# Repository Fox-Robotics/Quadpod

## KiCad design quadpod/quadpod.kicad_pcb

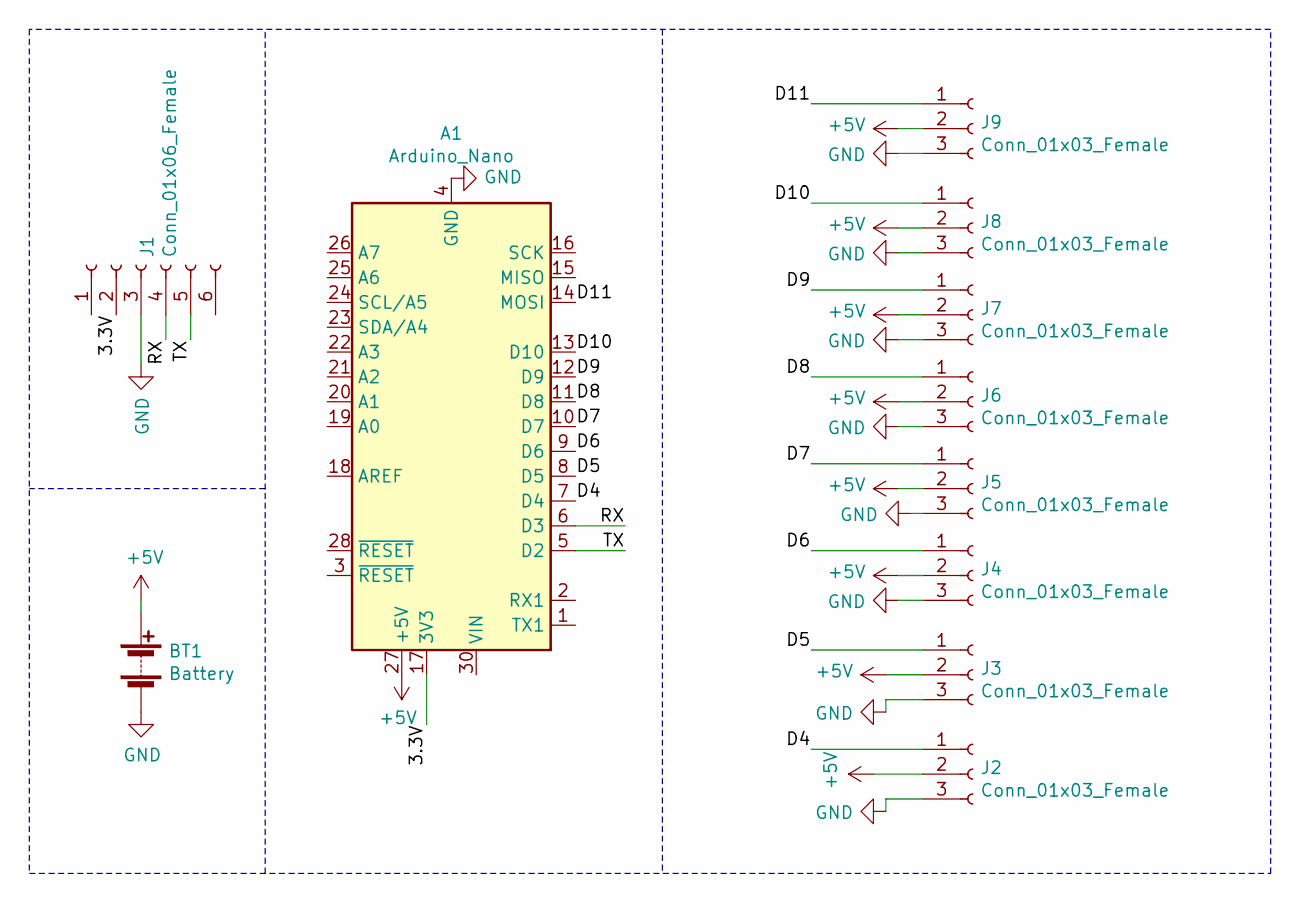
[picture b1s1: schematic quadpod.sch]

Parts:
A1: Arduino_Nano
BT1: Battery; Arduino_Nano
J1: Conn_01x06_Female; Pin_Header_Straight_1x06_Pitch1.27mm
J2, J3, J4, J5, J6, J7, J8, J9: Conn_01x03_Female; Pin_Header_Straight_1x03_Pitch1.27mm

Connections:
+5V: A1.27 (+5V), BT1.1 (+), J2.2, J3.2, J4.2, J5.2, J6.2, J7.2, J8.2, J9.2
/3.3V: A1.17 (3V3), J1.2
/D4: A1.7 (D4), J2.1
/D5: A1.8 (D5), J3.1
/D6: A1.9 (D6), J4.1
/D7: A1.10 (D7), J5.1
/D8: A1.11 (D8), J6.1
/D9: A1.12 (D9), J7.1
/D10: A1.13 (D10), J8.1
/D11: A1.14 (MOSI), J9.1
/RX: A1.6 (D3), J1.4
/TX: A1.5 (D2), J1.5
GND: A1.4 (GND), A1.29 (GND), BT1.2 (-), J1.3, J2.3, J3.3, J4.3, J5.3, J6.3, J7.3, J8.3, J9.3

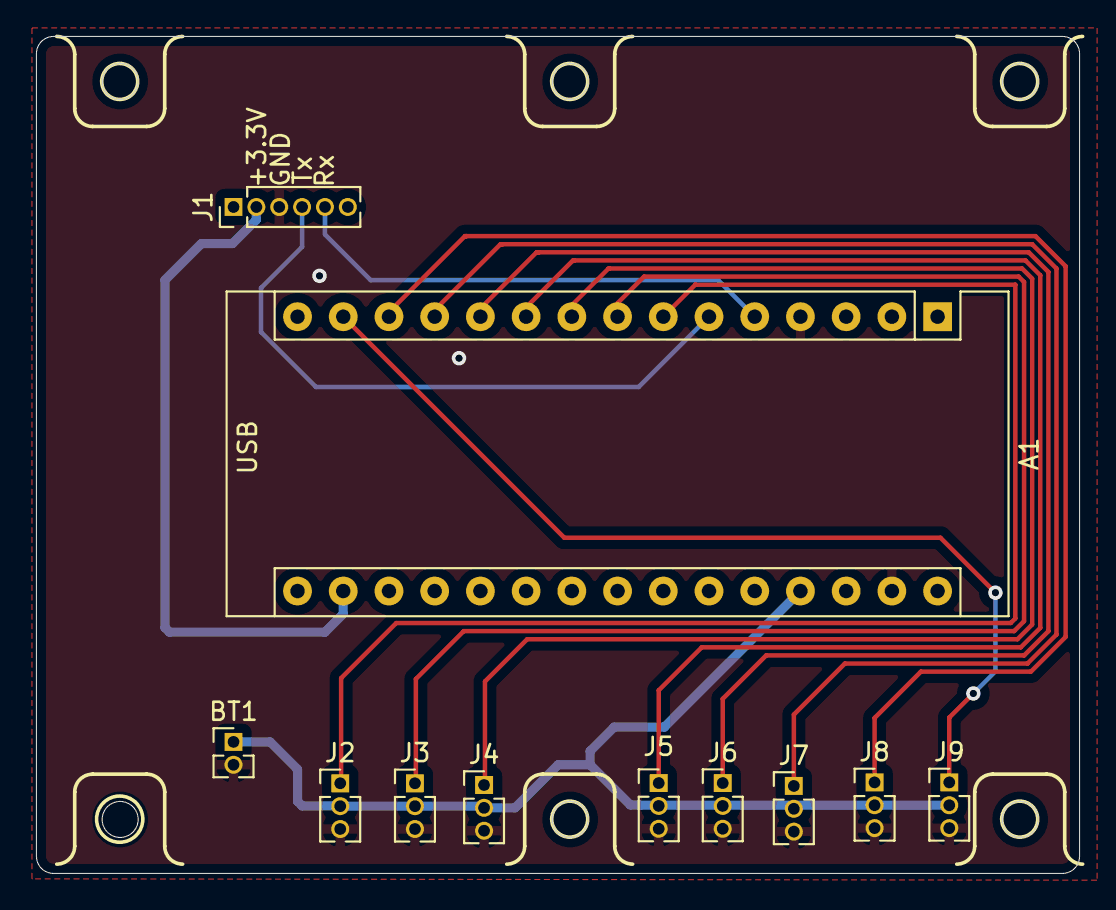
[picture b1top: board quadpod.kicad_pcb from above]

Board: 2 copper layers, 58.0 x 46.5 mm, 11 parts (0 on the bottom side), 13 nets.
